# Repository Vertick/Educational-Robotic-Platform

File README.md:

# Educational-Robotic-Platform
A platform to be used in Educational Robotic environment.
The Educational-Robotic-Platform (HeCRE) global architecture includes a Main Module and four Secondary Modules. HeCRE consists of up to four Secondary Modules. Each of these modules is formed by other components that are mentioned in the following subsections. The Main Module includes the FPGA prototype, a Bluetooth communications module, an Arduino Shield port and four Secondary Modules. An Arduino NANO and an Arduino Shield port are part of the Seconday Modules.
There are three design layers including hardware, firmware and software. The Main Module and Secondary Modules are hardware, FPGA firmware is the firmware and Arduino NANO boards software. Furthermore.

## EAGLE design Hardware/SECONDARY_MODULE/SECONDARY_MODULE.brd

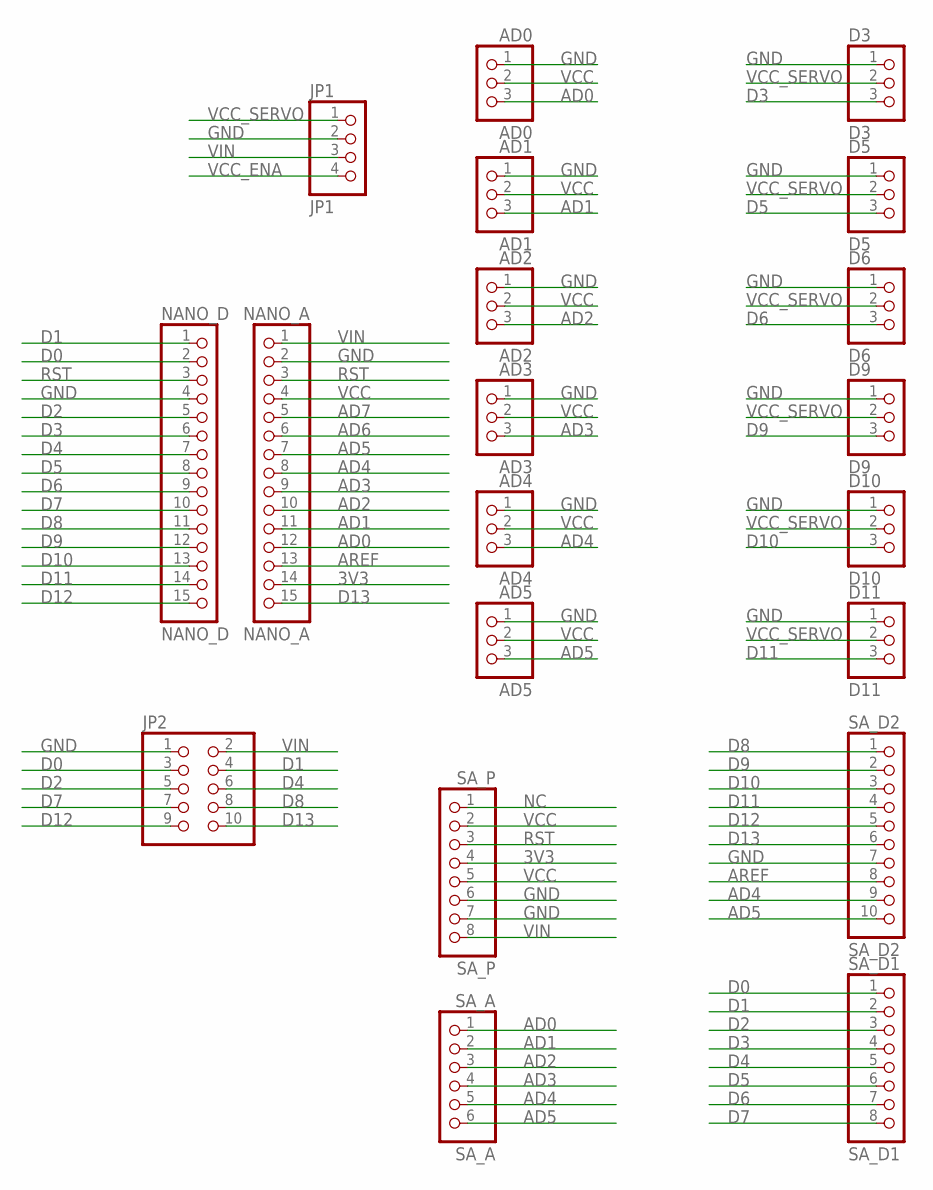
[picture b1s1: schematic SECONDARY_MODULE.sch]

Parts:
AD0: AD0; 1X03
AD1: AD1; 1X03
AD2: AD2; 1X03
AD3: AD3; 1X03
AD4: AD4; 1X03
AD5: AD5; 1X03
D3: D3; 1X03
D5: D5; 1X03
D6: D6; 1X03
D9: D9; 1X03
D10: D10; 1X03
D11: D11; 1X03
JP1: JP1; 1X04
JP2: PINHD-2X5; 2X05
NANO_A: NANO_A; 1X15
NANO_D: NANO_D; 1X15
SA_A: SA_A; 1X06
SA_D1: SA_D1; 1X08
SA_D2: SA_D2; 1X10
SA_P: SA_P; 1X08

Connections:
3V3: NANO_A.14, SA_P.4
AD0: AD0.3, NANO_A.12, SA_A.1
AD1: AD1.3, NANO_A.11, SA_A.2
AD2: AD2.3, NANO_A.10, SA_A.3
AD3: AD3.3, NANO_A.9, SA_A.4
AD4: AD4.3, NANO_A.8, SA_A.5, SA_D2.9
AD5: AD5.3, NANO_A.7, SA_A.6, SA_D2.10
AD6: NANO_A.6
AD7: NANO_A.5
AREF: NANO_A.13, SA_D2.8
D0: JP2.3, NANO_D.2, SA_D1.1
D1: JP2.4, NANO_D.1, SA_D1.2
D2: JP2.5, NANO_D.5, SA_D1.3
D3: D3.3, NANO_D.6, SA_D1.4
D4: JP2.6, NANO_D.7, SA_D1.5
D5: D5.3, NANO_D.8, SA_D1.6
D6: D6.3, NANO_D.9, SA_D1.7
D7: JP2.7, NANO_D.10, SA_D1.8
D8: JP2.8, NANO_D.11, SA_D2.1
D9: D9.3, NANO_D.12, SA_D2.2
D10: D10.3, NANO_D.13, SA_D2.3
D11: D11.3, NANO_D.14, SA_D2.4
D12: JP2.9, NANO_D.15, SA_D2.5
D13: JP2.10, NANO_A.15, SA_D2.6
GND: AD0.1, AD1.1, AD2.1, AD3.1, AD4.1, AD5.1, D3.1, D5.1, D6.1, D9.1, D10.1, D11.1, JP1.2, JP2.1, NANO_A.2, NANO_D.4, SA_D2.7, SA_P.6, SA_P.7
NC: SA_P.1
RST: NANO_A.3, NANO_D.3, SA_P.3
VCC: AD0.2, AD1.2, AD2.2, AD3.2, AD4.2, AD5.2, NANO_A.4, SA_P.2, SA_P.5
VCC_ENA: JP1.4
VCC_SERVO: D3.2, D5.2, D6.2, D9.2, D10.2, D11.2, JP1.1
VIN: JP1.3, JP2.2, NANO_A.1, SA_P.8

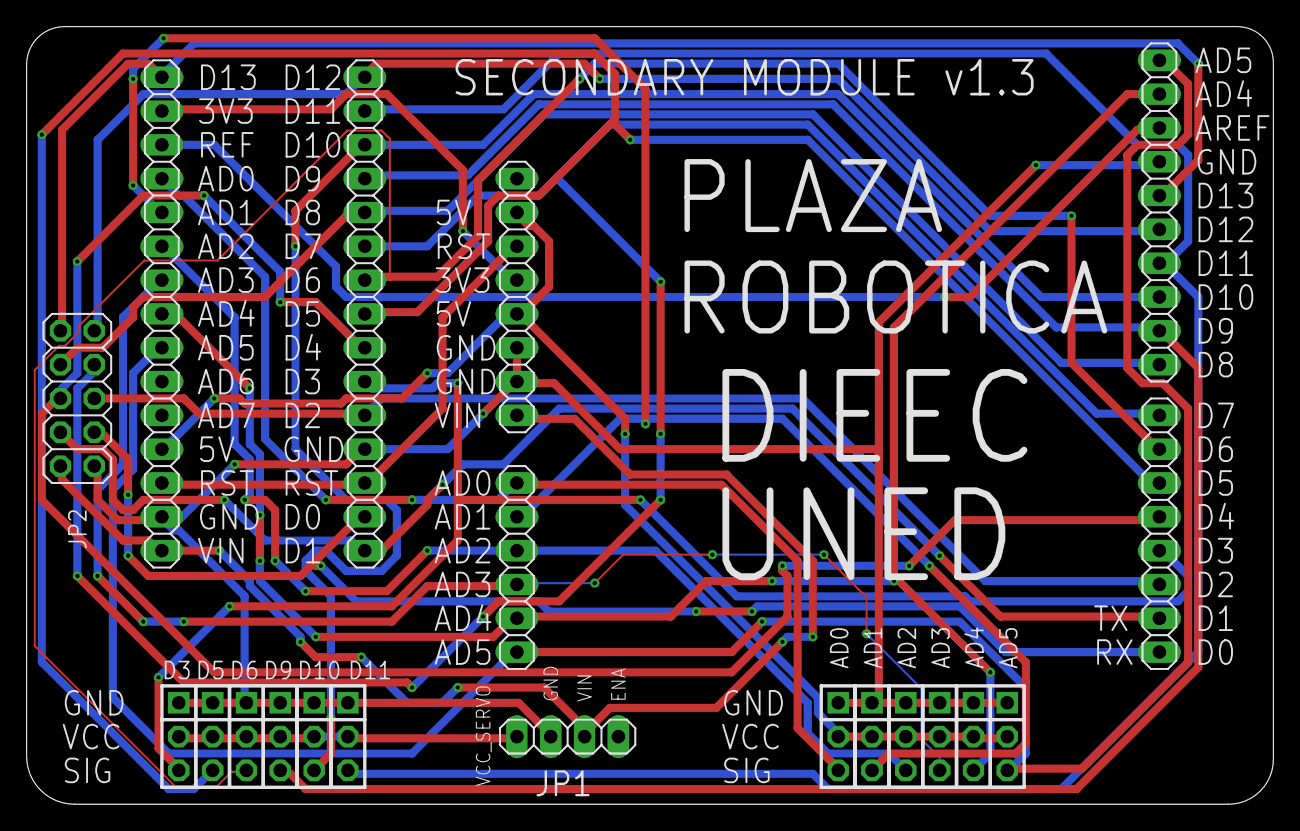
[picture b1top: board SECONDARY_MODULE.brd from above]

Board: 2 copper layers, 93.7 x 58.4 mm, 20 parts (0 on the bottom side), 27 nets.

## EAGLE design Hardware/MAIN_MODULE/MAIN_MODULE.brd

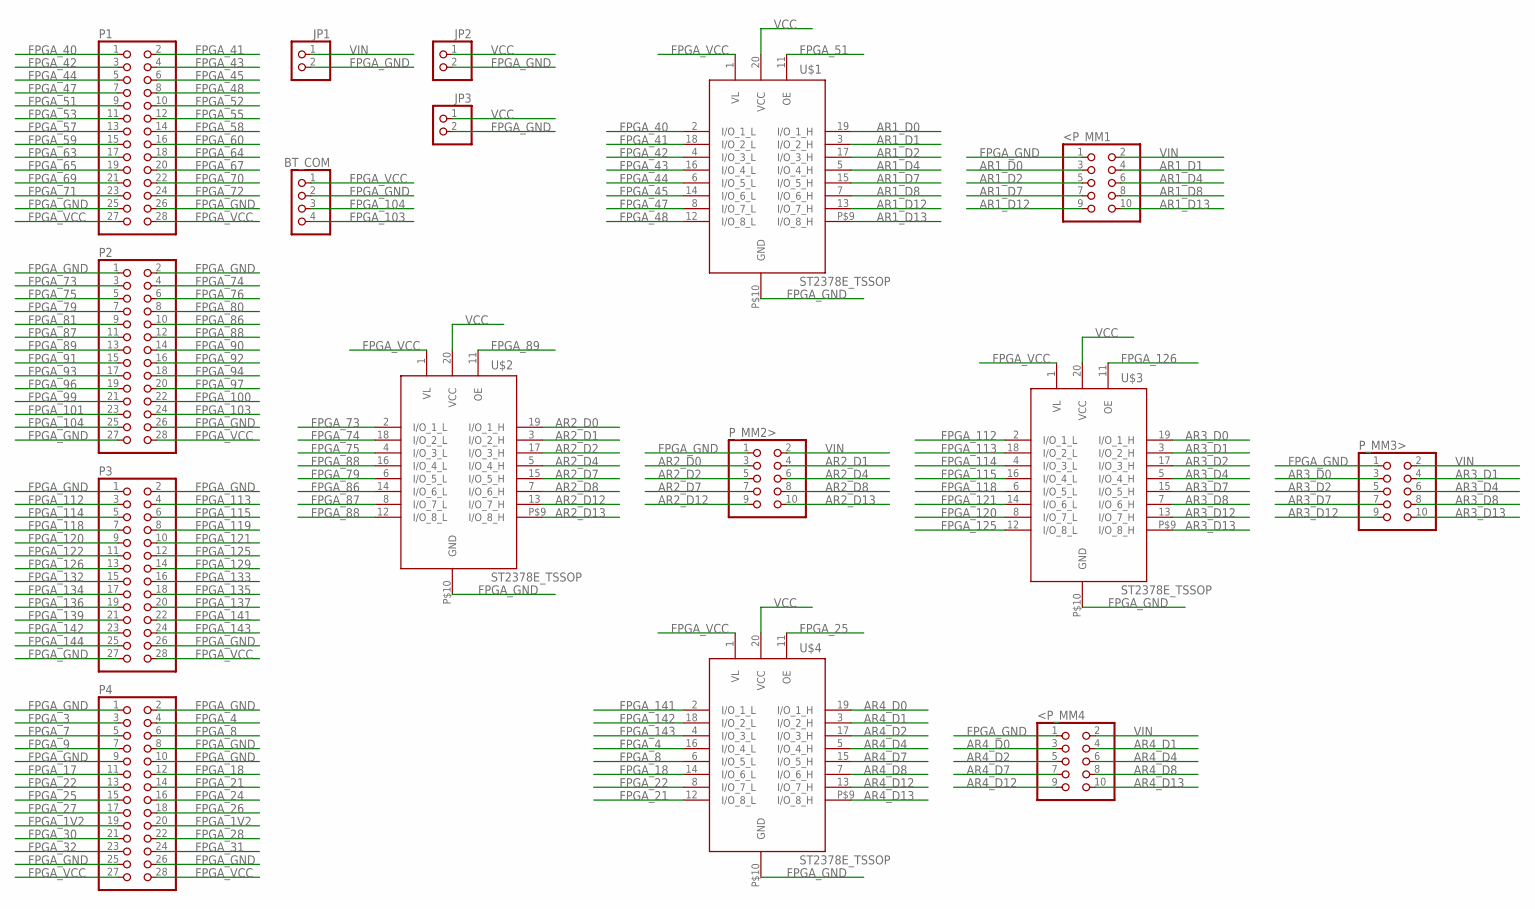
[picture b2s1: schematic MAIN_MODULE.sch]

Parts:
<P_MM1, <P_MM4: PINHD-2X5; 2X05
BT_COM: PINHD-1X4; 1X04
JP1, JP2, JP3: PINHD-1X2; 1X02
P1, P2, P3, P4: PINHD-2X14; 2X14
P_MM2>, P_MM3>: PINHD-2X5; 2X05
U$1, U$2, U$3, U$4: ST2378E_TSSOP; TSSOP20

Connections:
AR1_D0: <P_MM1.3, U$1.19 (I/O_1_H)
AR1_D1: <P_MM1.4, U$1.3 (I/O_2_H)
AR1_D2: <P_MM1.5, U$1.17 (I/O_3_H)
AR1_D4: <P_MM1.6, U$1.5 (I/O_4_H)
AR1_D7: <P_MM1.7, U$1.15 (I/O_5_H)
AR1_D8: <P_MM1.8, U$1.7 (I/O_6_H)
AR1_D12: <P_MM1.9, U$1.13 (I/O_7_H)
AR1_D13: <P_MM1.10, U$1.P$9 (I/O_8_H)
AR2_D0: P_MM2>.3, U$2.19 (I/O_1_H)
AR2_D1: P_MM2>.4, U$2.3 (I/O_2_H)
AR2_D2: P_MM2>.5, U$2.17 (I/O_3_H)
AR2_D4: P_MM2>.6, U$2.5 (I/O_4_H)
AR2_D7: P_MM2>.7, U$2.15 (I/O_5_H)
AR2_D8: P_MM2>.8, U$2.7 (I/O_6_H)
AR2_D12: P_MM2>.9, U$2.13 (I/O_7_H)
AR2_D13: P_MM2>.10, U$2.P$9 (I/O_8_H)
AR3_D0: P_MM3>.3, U$3.19 (I/O_1_H)
AR3_D1: P_MM3>.4, U$3.3 (I/O_2_H)
AR3_D2: P_MM3>.5, U$3.17 (I/O_3_H)
AR3_D4: P_MM3>.6, U$3.5 (I/O_4_H)
AR3_D7: P_MM3>.7, U$3.15 (I/O_5_H)
AR3_D8: P_MM3>.8, U$3.7 (I/O_6_H)
AR3_D12: P_MM3>.9, U$3.13 (I/O_7_H)
AR3_D13: P_MM3>.10, U$3.P$9 (I/O_8_H)
AR4_D0: <P_MM4.3, U$4.19 (I/O_1_H)
AR4_D1: <P_MM4.4, U$4.3 (I/O_2_H)
AR4_D2: <P_MM4.5, U$4.17 (I/O_3_H)
AR4_D4: <P_MM4.6, U$4.5 (I/O_4_H)
AR4_D7: <P_MM4.7, U$4.15 (I/O_5_H)
AR4_D8: <P_MM4.8, U$4.7 (I/O_6_H)
AR4_D12: <P_MM4.9, U$4.13 (I/O_7_H)
AR4_D13: <P_MM4.10, U$4.P$9 (I/O_8_H)
FPGA_1V2: P4.19, P4.20
FPGA_3: P4.3
FPGA_4: P4.4, U$4.16 (I/O_4_L)
FPGA_7: P4.5
FPGA_8: P4.6, U$4.6 (I/O_5_L)
FPGA_9: P4.7
FPGA_17: P4.11
FPGA_18: P4.12, U$4.14 (I/O_6_L)
FPGA_21: P4.14, U$4.12 (I/O_8_L)
FPGA_22: P4.13, U$4.8 (I/O_7_L)
FPGA_24: P4.16
FPGA_25: P4.15, U$4.11 (OE)
FPGA_26: P4.18
FPGA_27: P4.17
FPGA_28: P4.22
FPGA_30: P4.21
FPGA_31: P4.24
FPGA_32: P4.23
FPGA_40: P1.1, U$1.2 (I/O_1_L)
FPGA_41: P1.2, U$1.18 (I/O_2_L)
FPGA_42: P1.3, U$1.4 (I/O_3_L)
FPGA_43: P1.4, U$1.16 (I/O_4_L)
FPGA_44: P1.5, U$1.6 (I/O_5_L)
FPGA_45: P1.6, U$1.14 (I/O_6_L)
FPGA_47: P1.7, U$1.8 (I/O_7_L)
FPGA_48: P1.8, U$1.12 (I/O_8_L)
FPGA_51: P1.9, U$1.11 (OE)
FPGA_52: P1.10
FPGA_53: P1.11
FPGA_55: P1.12
FPGA_57: P1.13
FPGA_58: P1.14
FPGA_59: P1.15
FPGA_60: P1.16
FPGA_63: P1.17
FPGA_64: P1.18
FPGA_65: P1.19
FPGA_67: P1.20
FPGA_69: P1.21
FPGA_70: P1.22
FPGA_71: P1.23
FPGA_72: P1.24
FPGA_73: P2.3, U$2.2 (I/O_1_L)
FPGA_74: P2.4, U$2.18 (I/O_2_L)
FPGA_75: P2.5, U$2.4 (I/O_3_L)
FPGA_76: P2.6
FPGA_79: P2.7, U$2.6 (I/O_5_L)
FPGA_80: P2.8
FPGA_81: P2.9
FPGA_86: P2.10, U$2.14 (I/O_6_L)
FPGA_87: P2.11, U$2.8 (I/O_7_L)
FPGA_88: P2.12, U$2.12 (I/O_8_L), U$2.16 (I/O_4_L)
FPGA_89: P2.13, U$2.11 (OE)
FPGA_90: P2.14
FPGA_91: P2.15
FPGA_92: P2.16
FPGA_93: P2.17
FPGA_94: P2.18
FPGA_96: P2.19
FPGA_97: P2.20
FPGA_99: P2.21
FPGA_100: P2.22
FPGA_101: P2.23
FPGA_103: BT_COM.4, P2.24
FPGA_104: BT_COM.3, P2.25
FPGA_112: P3.3, U$3.2 (I/O_1_L)
FPGA_113: P3.4, U$3.18 (I/O_2_L)
FPGA_114: P3.5, U$3.4 (I/O_3_L)
FPGA_115: P3.6, U$3.16 (I/O_4_L)
FPGA_118: P3.7, U$3.6 (I/O_5_L)
FPGA_119: P3.8
FPGA_120: P3.9, U$3.8 (I/O_7_L)
FPGA_121: P3.10, U$3.14 (I/O_6_L)
FPGA_122: P3.11
FPGA_125: P3.12, U$3.12 (I/O_8_L)
FPGA_126: P3.13, U$3.11 (OE)
FPGA_129: P3.14
FPGA_132: P3.15
FPGA_133: P3.16
FPGA_134: P3.17
FPGA_135: P3.18
FPGA_136: P3.19
FPGA_137: P3.20
FPGA_139: P3.21
FPGA_141: P3.22, U$4.2 (I/O_1_L)
FPGA_142: P3.23, U$4.18 (I/O_2_L)
FPGA_143: P3.24, U$4.4 (I/O_3_L)
FPGA_144: P3.25
FPGA_GND: <P_MM1.1, <P_MM4.1, BT_COM.2, JP1.2, JP2.2, JP3.2, P1.25, P1.26, P2.1, P2.2, P2.26, P2.27, P3.1, P3.2, P3.26, P3.27, P4.1, P4.2, P4.8, P4.9, P4.10, P4.25, P4.26, P_MM2>.1, P_MM3>.1, U$1.P$10 (GND), U$2.P$10 (GND), U$3.P$10 (GND), U$4.P$10 (GND)
FPGA_VCC: BT_COM.1, P1.27, P1.28, P2.28, P3.28, P4.27, P4.28, U$1.1 (VL), U$2.1 (VL), U$3.1 (VL), U$4.1 (VL)
VCC: JP2.1, JP3.1, U$1.20 (VCC), U$2.20 (VCC), U$3.20 (VCC), U$4.20 (VCC)
VIN: <P_MM1.2, <P_MM4.2, JP1.1, P_MM2>.2, P_MM3>.2

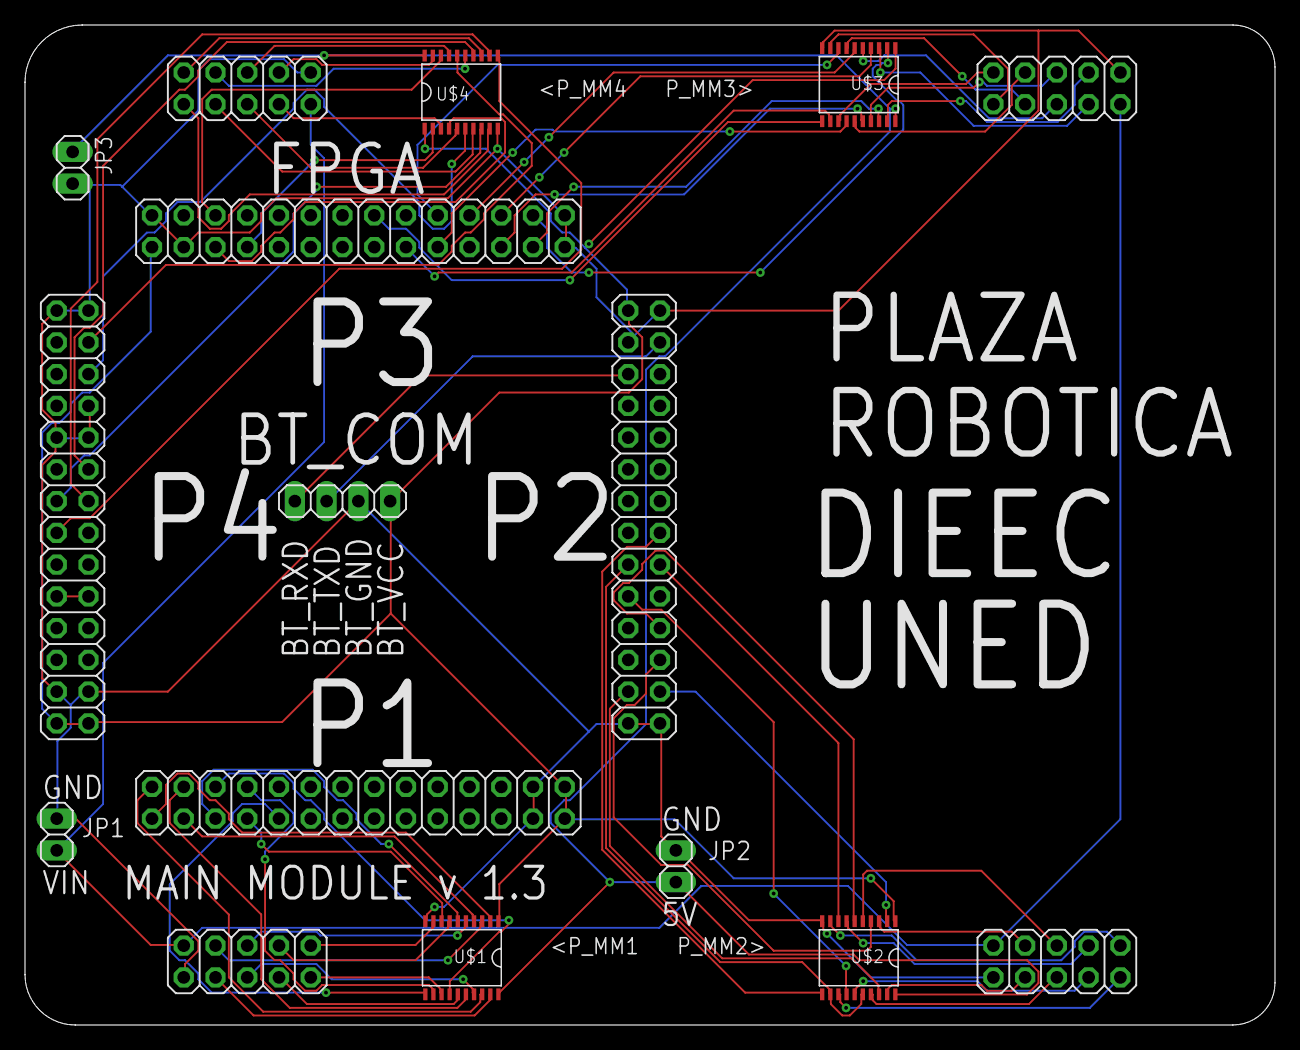
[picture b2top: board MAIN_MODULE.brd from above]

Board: 2 copper layers, 100.0 x 80.0 mm, 16 parts (0 on the bottom side), 74 nets.

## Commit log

2015-09-13 Create Test file
2019-01-31 Create LICENSE
2019-02-01 Remove files
2019-02-01 Remove files and folders
2019-02-01 Updated firmware files for v1, v2 and v3
2019-02-01 Updated software files for v1.0
